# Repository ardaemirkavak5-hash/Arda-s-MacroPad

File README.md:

-Arda's Macro Pad;

Hello. I am Arda this is my project a custom Macro Pad.

-Project Folders
I organized everything into folders to keep it clean, as requested:

PCB: You can find my KiCad files here (schematic and board layout). I also added a PDF of the schematic if you don't have KiCad installed.
CAD: This folder has the 3D models for the case and the top plate. I'm planning to 3D print these.
Images: I've uploaded screenshots of my PCB, the schematic, and some 3D renders so you can see the final look.
Firmware: My `code.py` file is in this folder.

-Components I Used
Seeed Studio XIAO
Mechanical Switches
3D Printed Case (Top and Bottom)

I've updated everything based on the feedback. Hope it looks good now.

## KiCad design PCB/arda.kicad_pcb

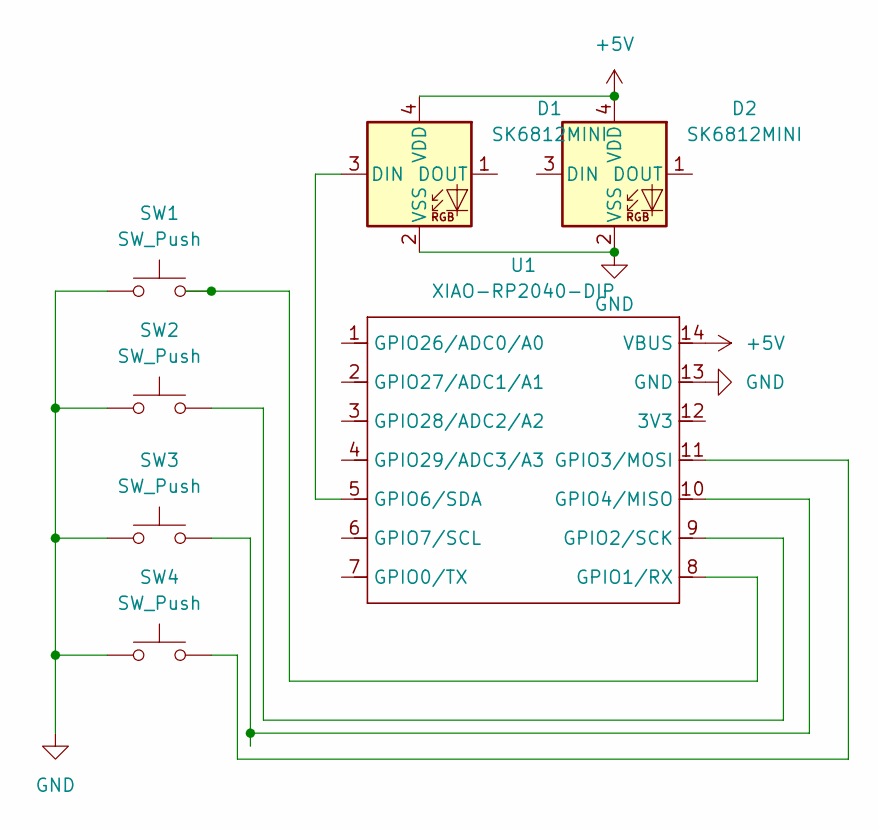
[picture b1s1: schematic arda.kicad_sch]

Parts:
D1, D2: SK6812MINI; LED_SK6812MINI_PLCC4_3.5x3.5mm_P1.75mm
SW1, SW2, SW3, SW4: SW_Push; SW_Cherry_MX_1.00u_PCB
U1: XIAO-RP2040-DIP

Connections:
+5V: D1.4 (VDD), D2.4 (VDD), U1.14 (VBUS)
GND: D1.2 (VSS), D2.2 (VSS), SW1.1, SW2.1, SW3.1, SW4.1, U1.13 (GND)
unnamed: D1.3 (DIN), U1.5 (GPIO6/SDA)
unnamed: SW1.2, U1.8 (GPIO1/RX)
unnamed: SW2.2, U1.9 (GPIO2/SCK)
unnamed: SW4.2, U1.11 (GPIO3/MOSI)
unnamed: SW3.2, U1.10 (GPIO4/MISO)

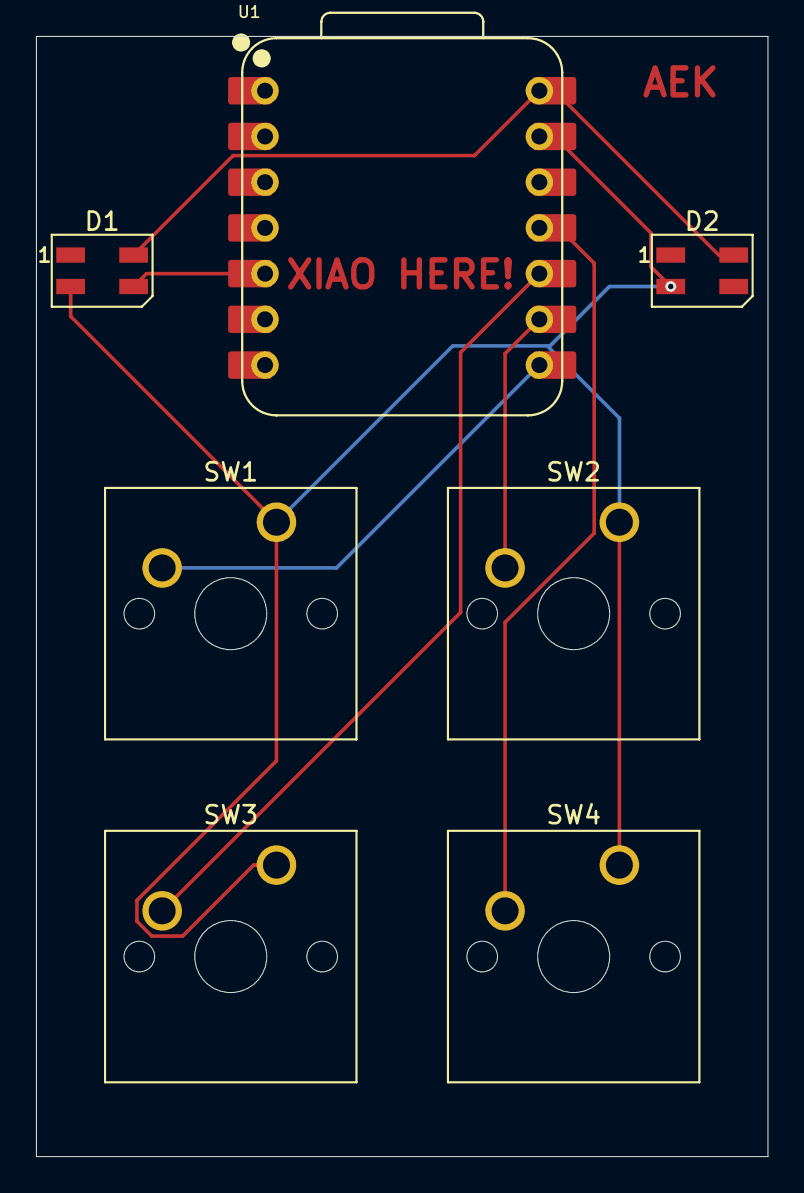
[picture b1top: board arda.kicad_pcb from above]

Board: 2 copper layers, 40.6 x 62.2 mm, 7 parts (0 on the bottom side), 7 nets.
